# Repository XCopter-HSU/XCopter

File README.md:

# XCopter
This is the (main) repository for the XCopter Project from HSU

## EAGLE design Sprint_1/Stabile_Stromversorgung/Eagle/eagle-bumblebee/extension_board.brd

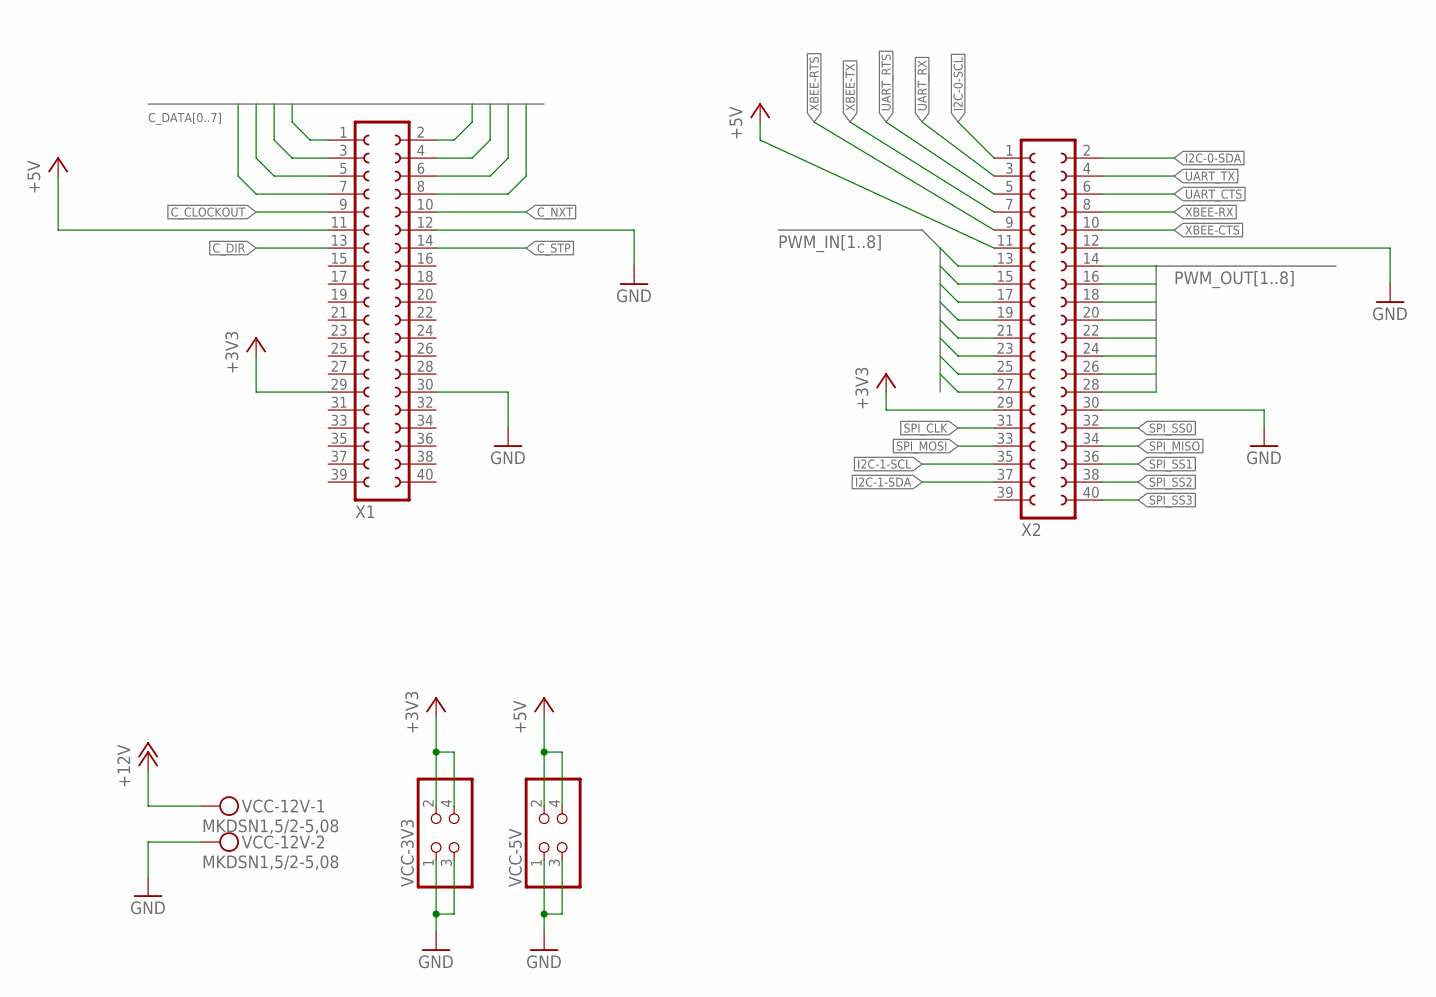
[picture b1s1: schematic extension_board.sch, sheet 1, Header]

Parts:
VCC-3V3, VCC-5V: PINHD-2X2; 2X02
VCC-12V: MKDSN1,5/2-5,08
X1, X2: FE20-2

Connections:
+3V3: VCC-3V3.2, VCC-3V3.4, X1.29, X2.29; also elsewhere on the board
+5V: VCC-5V.2, VCC-5V.4, X1.11, X2.11; also elsewhere on the board
+12V: VCC-12V.1; also elsewhere on the board
C_CLOCKOUT: X1.9; also elsewhere on the board
C_DATA0: X1.1; also elsewhere on the board
C_DATA1: X1.3; also elsewhere on the board
C_DATA2: X1.5; also elsewhere on the board
C_DATA3: X1.7; also elsewhere on the board
C_DATA4: X1.2; also elsewhere on the board
C_DATA5: X1.4; also elsewhere on the board
C_DATA6: X1.6; also elsewhere on the board
C_DATA7: X1.8; also elsewhere on the board
C_DIR: X1.13; also elsewhere on the board
C_NXT: X1.10; also elsewhere on the board
C_STP: X1.14; also elsewhere on the board
GND: VCC-3V3.1, VCC-3V3.3, VCC-5V.1, VCC-5V.3, VCC-12V.2, X1.12, X1.30, X2.12, X2.30; also elsewhere on the board
I2C-0-SCL: X2.1; also elsewhere on the board
I2C-0-SDA: X2.2; also elsewhere on the board
I2C-1-SCL: X2.35; also elsewhere on the board
I2C-1-SDA: X2.37; also elsewhere on the board
PWM_INPUT1: X2.13; also elsewhere on the board
PWM_INPUT2: X2.15; also elsewhere on the board
PWM_INPUT3: X2.17; also elsewhere on the board
PWM_INPUT4: X2.19; also elsewhere on the board
PWM_INPUT5: X2.21; also elsewhere on the board
PWM_INPUT6: X2.23; also elsewhere on the board
PWM_INPUT7: X2.25; also elsewhere on the board
PWM_INPUT8: X2.27; also elsewhere on the board
PWM_OUTPUT1: X2.28; also elsewhere on the board
PWM_OUTPUT2: X2.26; also elsewhere on the board
PWM_OUTPUT3: X2.24; also elsewhere on the board
PWM_OUTPUT4: X2.22; also elsewhere on the board
PWM_OUTPUT5: X2.20; also elsewhere on the board
PWM_OUTPUT6: X2.18; also elsewhere on the board
PWM_OUTPUT7: X2.16; also elsewhere on the board
PWM_OUTPUT8: X2.14; also elsewhere on the board
SPI_CLK: X2.31; also elsewhere on the board
SPI_MISO: X2.34; also elsewhere on the board
SPI_MOSI: X2.33; also elsewhere on the board
SPI_SS0: X2.32; also elsewhere on the board
SPI_SS1: X2.36; also elsewhere on the board
SPI_SS2: X2.38; also elsewhere on the board
SPI_SS3: X2.40; also elsewhere on the board
UART_CTS: X2.6; also elsewhere on the board
UART_RTS: X2.5; also elsewhere on the board
UART_RX: X2.3; also elsewhere on the board
UART_TX: X2.4; also elsewhere on the board
XBEE-CTS: X2.10; also elsewhere on the board
XBEE-RTS: X2.9; also elsewhere on the board
XBEE-RX: X2.8; also elsewhere on the board
XBEE-TX: X2.7; also elsewhere on the board

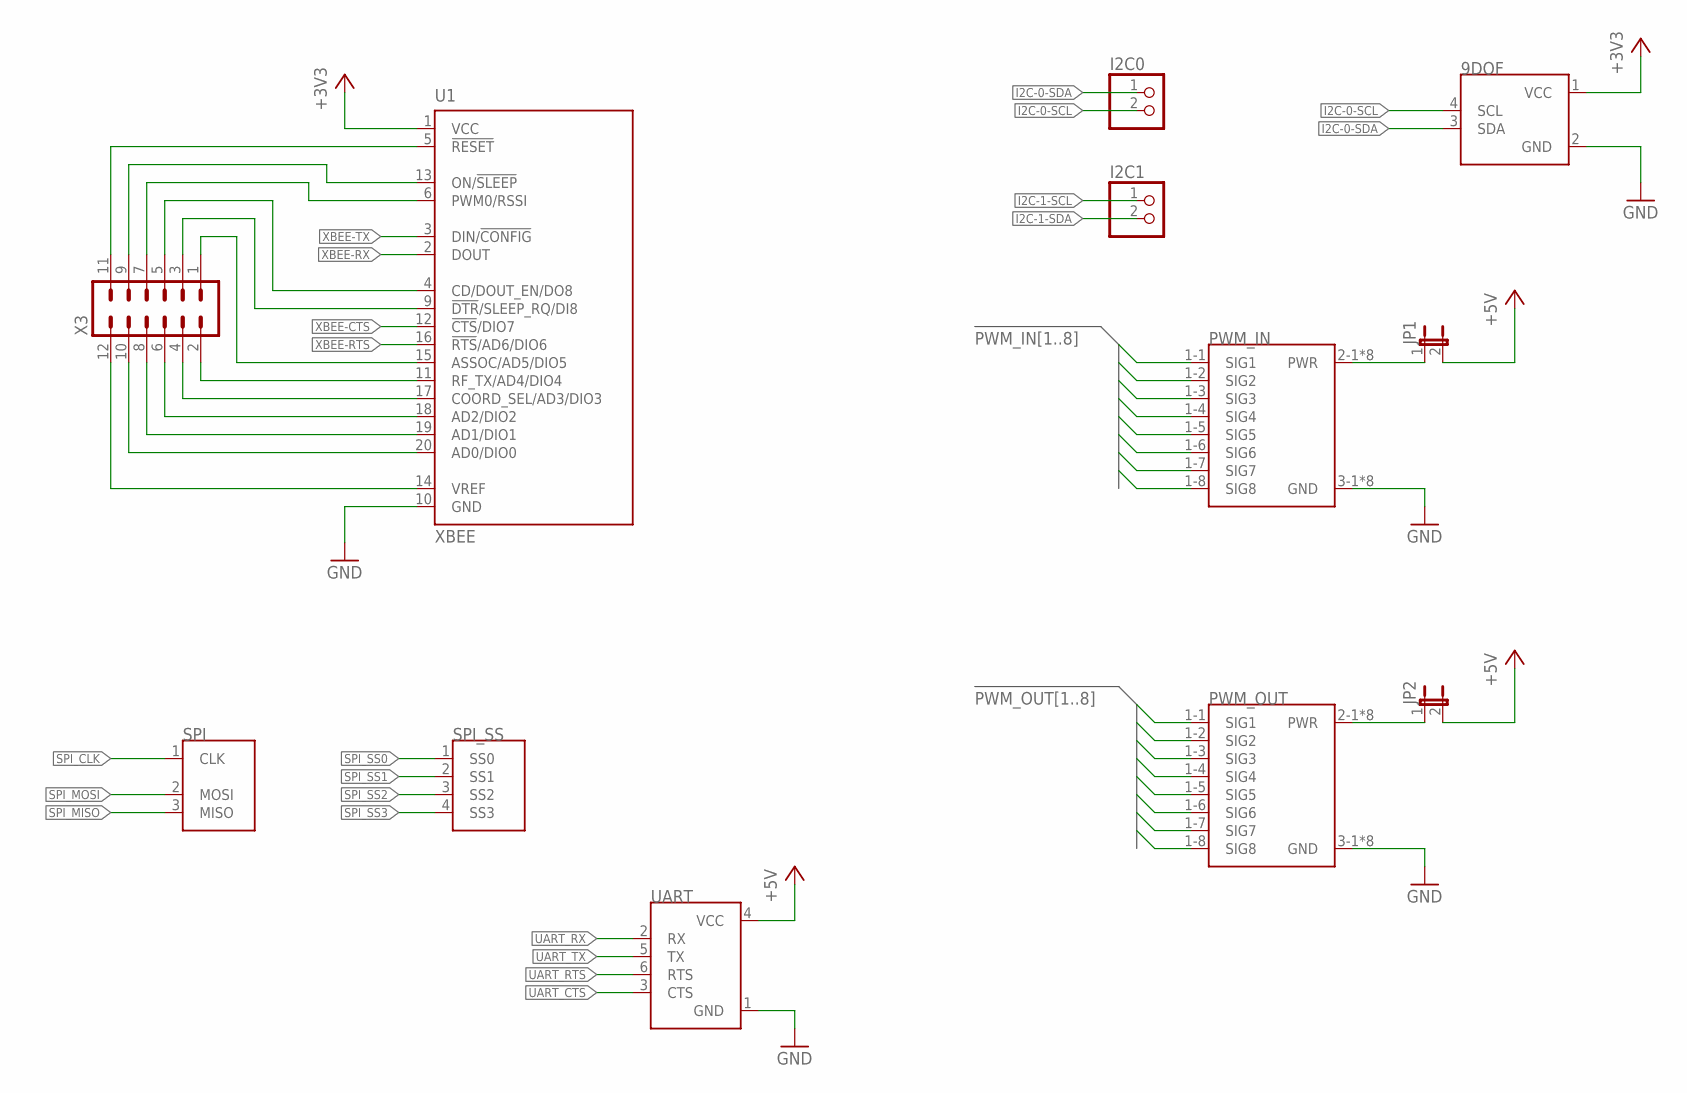
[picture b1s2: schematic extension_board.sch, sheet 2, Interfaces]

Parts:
9DOF: I2C; MA04-1
I2C0, I2C1: PINHD-1X2; 1X02
JP1, JP2: JP1E; JP1
PWM_IN: 8RX; MA08-3
PWM_OUT: 8RX; MA08-3
SPI: SPI_MAIN; MA03-1
SPI_SS: SPI_SS; MA04-1
U1: XBEE
UART: UART; MA03-2
X3: MA06-2

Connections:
+3V3: 9DOF.1 (VCC), U1.1 (VCC); also elsewhere on the board
+5V: JP1.2, JP2.2, UART.4 (VCC); also elsewhere on the board
GND: 9DOF.2 (GND), PWM_IN.3-1 (GND), PWM_IN.3-2 (GND), PWM_IN.3-3 (GND), PWM_IN.3-4 (GND), PWM_IN.3-5 (GND), PWM_IN.3-6 (GND), PWM_IN.3-7 (GND), PWM_IN.3-8 (GND), PWM_OUT.3-1 (GND), PWM_OUT.3-2 (GND), PWM_OUT.3-3 (GND), PWM_OUT.3-4 (GND), PWM_OUT.3-5 (GND), PWM_OUT.3-6 (GND), PWM_OUT.3-7 (GND), PWM_OUT.3-8 (GND), U1.10 (GND), UART.1 (GND); also elsewhere on the board
I2C-0-SCL: 9DOF.4 (SCL), I2C0.2; also elsewhere on the board
I2C-0-SDA: 9DOF.3 (SDA), I2C0.1; also elsewhere on the board
I2C-1-SCL: I2C1.1; also elsewhere on the board
I2C-1-SDA: I2C1.2; also elsewhere on the board
unnamed: JP1.1, PWM_IN.2-1 (PWR), PWM_IN.2-2 (PWR), PWM_IN.2-3 (PWR), PWM_IN.2-4 (PWR), PWM_IN.2-5 (PWR), PWM_IN.2-6 (PWR), PWM_IN.2-7 (PWR), PWM_IN.2-8 (PWR)
unnamed: JP2.1, PWM_OUT.2-1 (PWR), PWM_OUT.2-2 (PWR), PWM_OUT.2-3 (PWR), PWM_OUT.2-4 (PWR), PWM_OUT.2-5 (PWR), PWM_OUT.2-6 (PWR), PWM_OUT.2-7 (PWR), PWM_OUT.2-8 (PWR)
unnamed: U1.5 (!RESET), X3.11
unnamed: U1.14 (VREF), X3.12
unnamed: U1.20 (AD0/DIO0), X3.10
unnamed: U1.19 (AD1/DIO1), X3.8
unnamed: U1.18 (AD2/DIO2), X3.6
unnamed: U1.17 (COORD_SEL/AD3/DIO3), X3.4
unnamed: U1.11 (RF_TX/AD4/DIO4), X3.2
unnamed: U1.15 (ASSOC/AD5/DIO5), X3.1
unnamed: U1.9 (!DTR!/SLEEP_RQ/DI8), X3.3
unnamed: U1.4 (CD/DOUT_EN/DO8), X3.5
unnamed: U1.6 (PWM0/RSSI), X3.7
unnamed: U1.13 (ON/!SLEEP), X3.9
PWM_INPUT1: PWM_IN.1-1 (SIG1); also elsewhere on the board
PWM_INPUT2: PWM_IN.1-2 (SIG2); also elsewhere on the board
PWM_INPUT3: PWM_IN.1-3 (SIG3); also elsewhere on the board
PWM_INPUT4: PWM_IN.1-4 (SIG4); also elsewhere on the board
PWM_INPUT5: PWM_IN.1-5 (SIG5); also elsewhere on the board
PWM_INPUT6: PWM_IN.1-6 (SIG6); also elsewhere on the board
PWM_INPUT7: PWM_IN.1-7 (SIG7); also elsewhere on the board
PWM_INPUT8: PWM_IN.1-8 (SIG8); also elsewhere on the board
PWM_OUTPUT1: PWM_OUT.1-1 (SIG1); also elsewhere on the board
PWM_OUTPUT2: PWM_OUT.1-2 (SIG2); also elsewhere on the board
PWM_OUTPUT3: PWM_OUT.1-3 (SIG3); also elsewhere on the board
PWM_OUTPUT4: PWM_OUT.1-4 (SIG4); also elsewhere on the board
PWM_OUTPUT5: PWM_OUT.1-5 (SIG5); also elsewhere on the board
PWM_OUTPUT6: PWM_OUT.1-6 (SIG6); also elsewhere on the board
PWM_OUTPUT7: PWM_OUT.1-7 (SIG7); also elsewhere on the board
PWM_OUTPUT8: PWM_OUT.1-8 (SIG8); also elsewhere on the board
SPI_CLK: SPI.1 (CLK); also elsewhere on the board
SPI_MISO: SPI.3 (MISO); also elsewhere on the board
SPI_MOSI: SPI.2 (MOSI); also elsewhere on the board
SPI_SS0: SPI_SS.1 (SS0); also elsewhere on the board
SPI_SS1: SPI_SS.2 (SS1); also elsewhere on the board
SPI_SS2: SPI_SS.3 (SS2); also elsewhere on the board
SPI_SS3: SPI_SS.4 (SS3); also elsewhere on the board
UART_CTS: UART.3 (CTS); also elsewhere on the board
UART_RTS: UART.6 (RTS); also elsewhere on the board
UART_RX: UART.2 (RX); also elsewhere on the board
UART_TX: UART.5 (TX); also elsewhere on the board
XBEE-CTS: U1.12 (!CTS!/DIO7); also elsewhere on the board
XBEE-RTS: U1.16 (!RTS!/AD6/DIO6); also elsewhere on the board
XBEE-RX: U1.2 (DOUT); also elsewhere on the board
XBEE-TX: U1.3 (DIN/!CONFIG); also elsewhere on the board

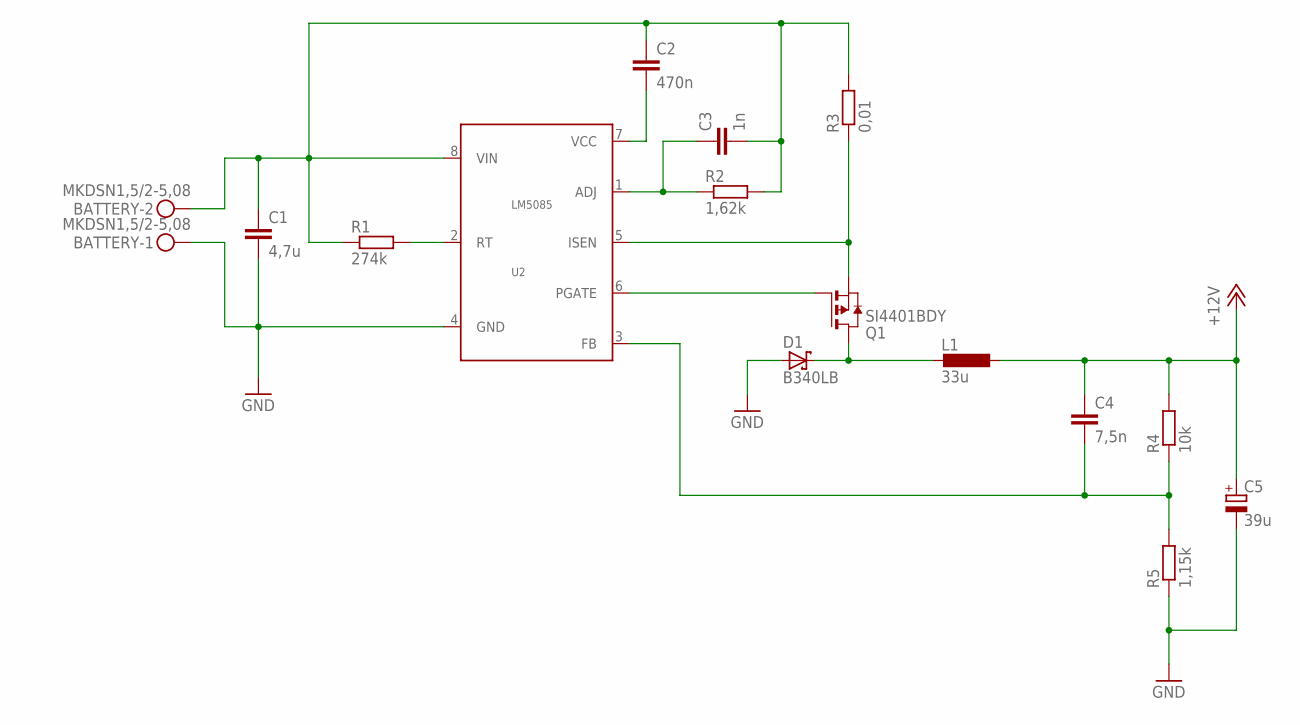
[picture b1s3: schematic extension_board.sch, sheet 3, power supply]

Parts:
BATTERY: MKDSN1,5/2-5,08
C1: 4,7u; C1206
C2: 470n; C1206
C3: 1n; C1206
C4: 7,5n; C1206
C5: 39u; SMC_B
D1: B340LB; SMB
L1: 33u; INDUKTOR
Q1: SI4401BDY; SO8-FET
R1: 274k; R1206
R2: 1,62k; R1206
R3: 0,01; R1206
R4: 10k; R1206
R5: 1,15k; R1206
U2: LM5085; S-PDSO-G08

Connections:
+12V: C4.1, C5.+, L1.P$2 (2), R4.2; also elsewhere on the board
GND: BATTERY.1, C1.2, C5.-, D1.A, R5.1, U2.4 (GND); also elsewhere on the board
unnamed: R1.2, U2.2 (RT)
unnamed: C2.2, U2.7 (VCC)
unnamed: C3.1, R2.1, U2.1 (ADJ)
unnamed: BATTERY.2, C1.1, C2.1, C3.2, R1.1, R2.2, R3.2, U2.8 (VIN)
unnamed: Q1.1 (S), Q1.2 (S), Q1.3 (S), R3.1, U2.5 (ISEN)
unnamed: C4.2, R4.1, R5.2, U2.3 (FB)
unnamed: Q1.4 (G), U2.6 (PGATE)
unnamed: D1.C, L1.P$1 (1), Q1.5 (D), Q1.6 (D), Q1.7 (D), Q1.8 (D), Q1.D1 (D), Q1.D2 (D), Q1.D3 (D)

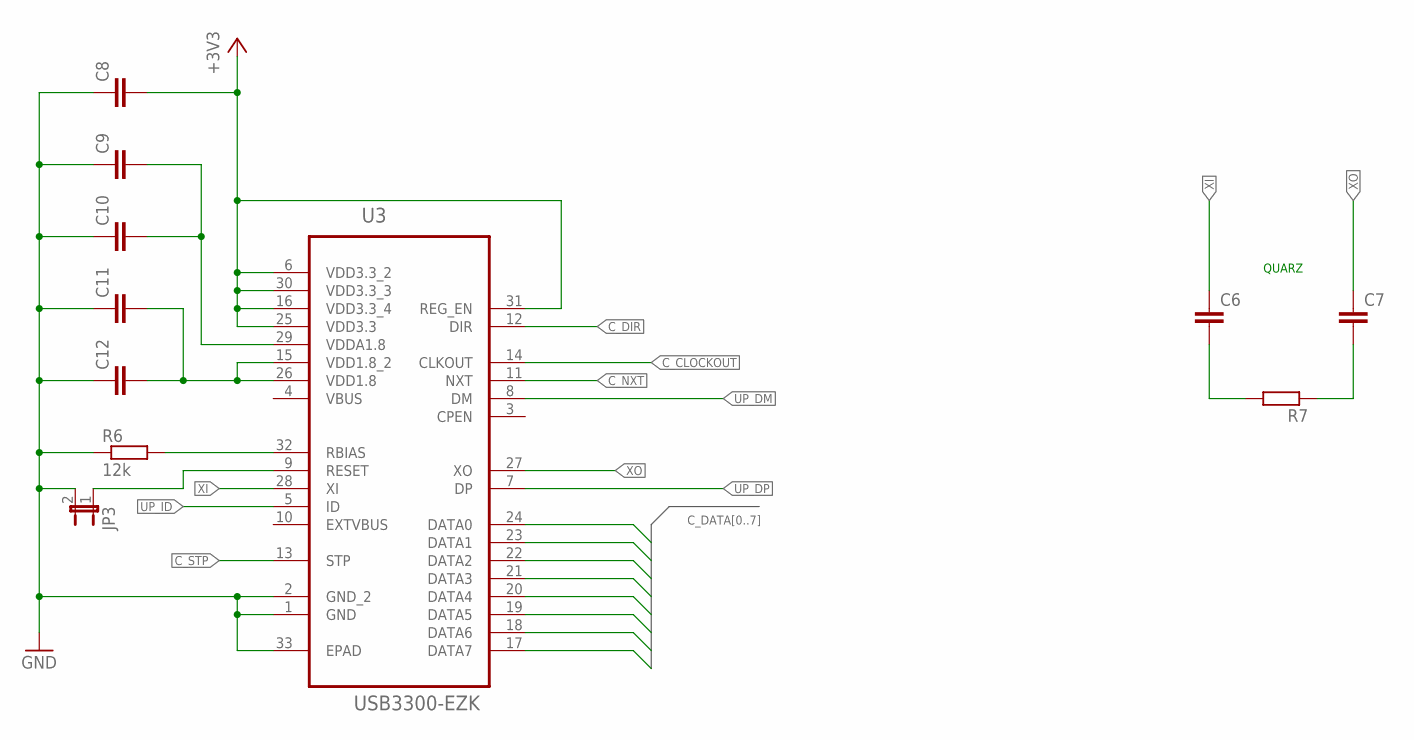
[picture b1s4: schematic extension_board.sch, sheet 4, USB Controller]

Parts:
C6, C7, C8, C9, C10, C11, C12: CC1206; C1206
JP3: JP1E; JP1
R6: 12k; R1206
R7: RR1206; R1206
U3: USB3300-EZK; QFN50P500X500X100-33N

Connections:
+3V3: C8.2, U3.6 (VDD3.3_2), U3.16 (VDD3.3_4), U3.25 (VDD3.3), U3.30 (VDD3.3_3), U3.31 (REG_EN); also elsewhere on the board
C_CLOCKOUT: U3.14 (CLKOUT); also elsewhere on the board
C_DATA0: U3.24 (DATA0); also elsewhere on the board
C_DATA1: U3.23 (DATA1); also elsewhere on the board
C_DATA2: U3.22 (DATA2); also elsewhere on the board
C_DATA3: U3.21 (DATA3); also elsewhere on the board
C_DATA4: U3.20 (DATA4); also elsewhere on the board
C_DATA5: U3.19 (DATA5); also elsewhere on the board
C_DATA6: U3.18 (DATA6); also elsewhere on the board
C_DATA7: U3.17 (DATA7); also elsewhere on the board
C_DIR: U3.12 (DIR); also elsewhere on the board
C_NXT: U3.11 (NXT); also elsewhere on the board
C_STP: U3.13 (STP); also elsewhere on the board
GND: C8.1, C9.1, C10.1, C11.1, C12.1, JP3.2, R6.1, U3.1 (GND), U3.2 (GND_2), U3.33 (EPAD); also elsewhere on the board
unnamed: C9.2, C10.2, U3.29 (VDDA1.8)
unnamed: R6.2, U3.32 (RBIAS)
unnamed: C6.2, R7.2
unnamed: C7.2, R7.1
unnamed: C11.2, C12.2, U3.15 (VDD1.8_2), U3.26 (VDD1.8)
unnamed: JP3.1, U3.9 (RESET)
UP_DM: U3.8 (DM)
UP_DP: U3.7 (DP)
UP_ID: U3.5 (ID)
VBUS: U3.4 (VBUS)
XI: C6.1, U3.28 (XI)
XO: C7.1, U3.27 (XO)

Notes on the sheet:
QUARZ

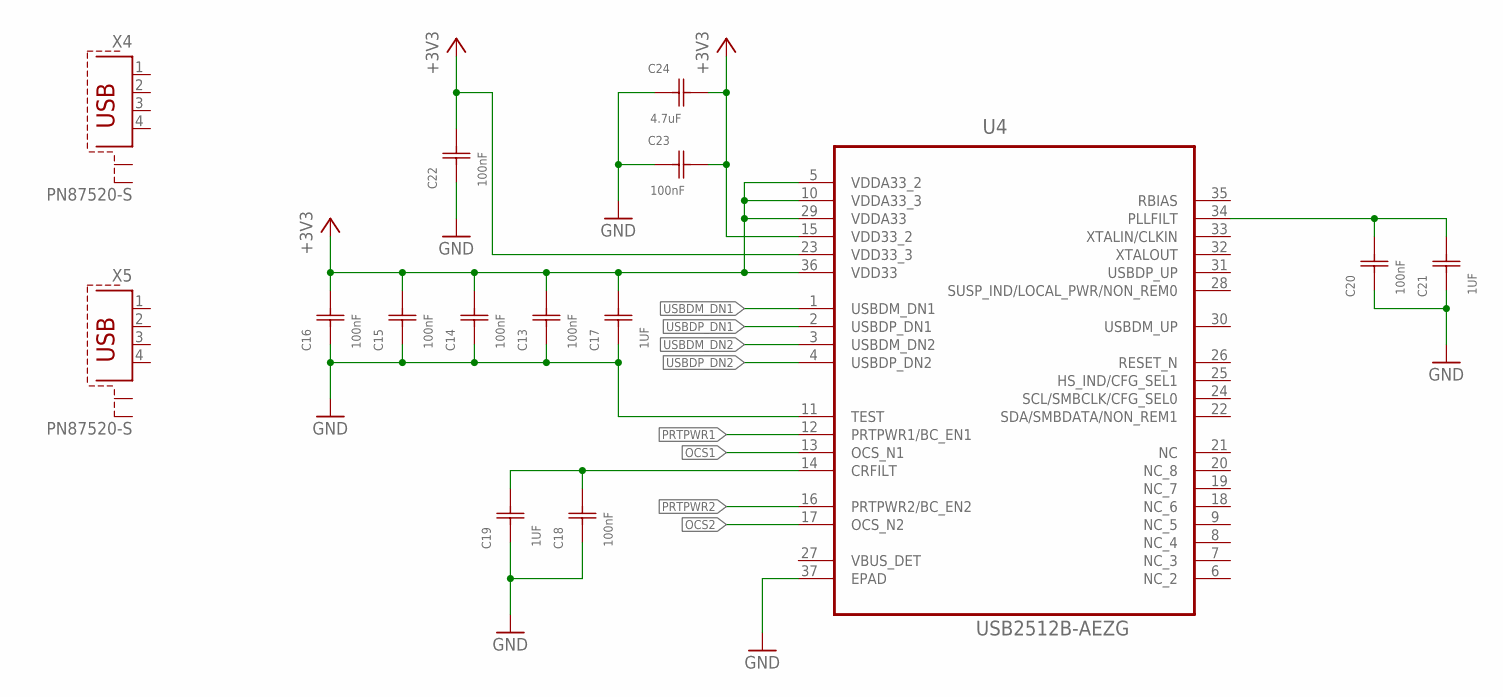
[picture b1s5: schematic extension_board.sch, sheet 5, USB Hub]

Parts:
C13, C14, C15, C16, C18, C20, C22, C23: 100nF; CAPC1608X90N
C17, C19, C21: 1UF; CAPC3216X127N
C24: 4.7uF; CAPC2013X140N
U4: USB2512B-AEZG; QFN50P600X600X100-37N
X4, X5: PN87520-S

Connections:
+3V3: C13.2 (C2), C14.2 (C2), C15.2 (C2), C16.2 (C2), C17.2 (C2), C22.2 (C2), C23.2 (C2), C24.2 (C2), U4.5 (VDDA33_2), U4.10 (VDDA33_3), U4.15 (VDD33_2), U4.23 (VDD33_3), U4.29 (VDDA33), U4.36 (VDD33); also elsewhere on the board
GND: C13.1 (C1), C14.1 (C1), C15.1 (C1), C16.1 (C1), C17.1 (C1), C18.1 (C1), C19.1 (C1), C20.1 (C1), C21.1 (C1), C22.1 (C1), C23.1 (C1), C24.1 (C1), U4.11 (TEST), U4.37 (EPAD); also elsewhere on the board
unnamed: C18.2 (C2), C19.2 (C2), U4.14 (CRFILT)
unnamed: C20.2 (C2), C21.2 (C2), U4.34 (PLLFILT)
OCS1: U4.13 (OCS_N1)
OCS2: U4.17 (OCS_N2)
PRTPWR1: U4.12 (PRTPWR1/BC_EN1)
PRTPWR2: U4.16 (PRTPWR2/BC_EN2)
USBDM_DN1: U4.1 (USBDM_DN1)
USBDM_DN2: U4.3 (USBDM_DN2)
USBDP_DN1: U4.2 (USBDP_DN1)
USBDP_DN2: U4.4 (USBDP_DN2)
VBUS_DET: U4.27 (VBUS_DET)

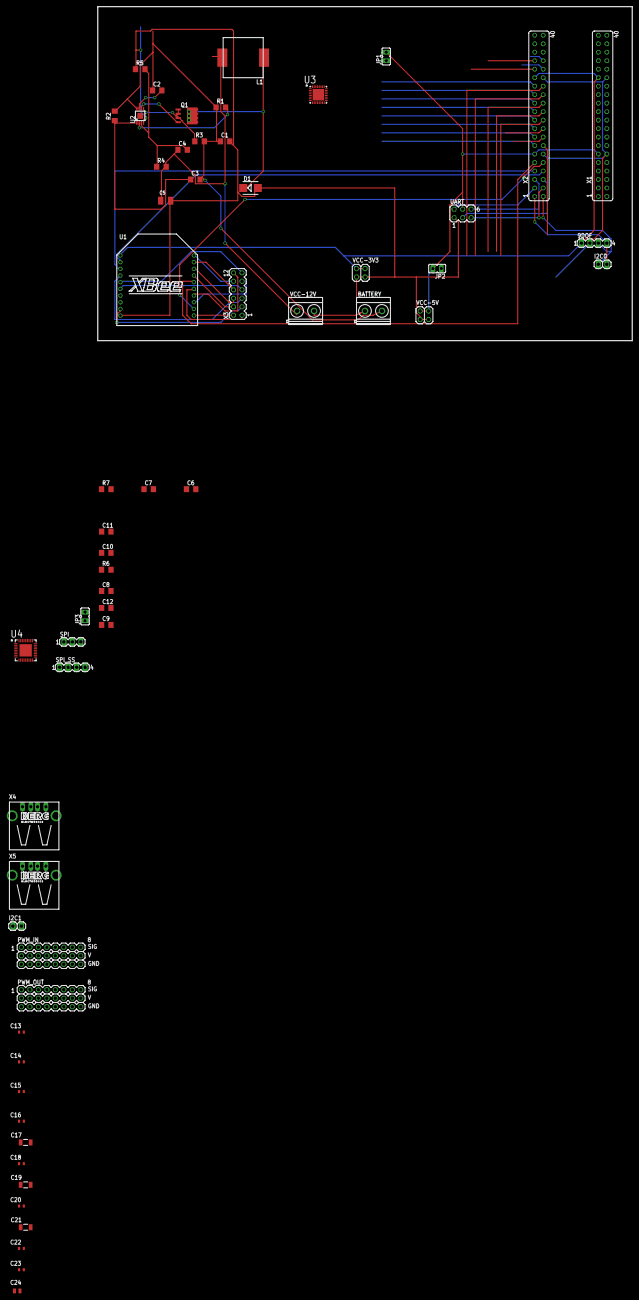
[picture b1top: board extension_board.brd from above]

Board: 2 copper layers, 160.0 x 100.0 mm, 58 parts (0 on the bottom side), 83 nets.

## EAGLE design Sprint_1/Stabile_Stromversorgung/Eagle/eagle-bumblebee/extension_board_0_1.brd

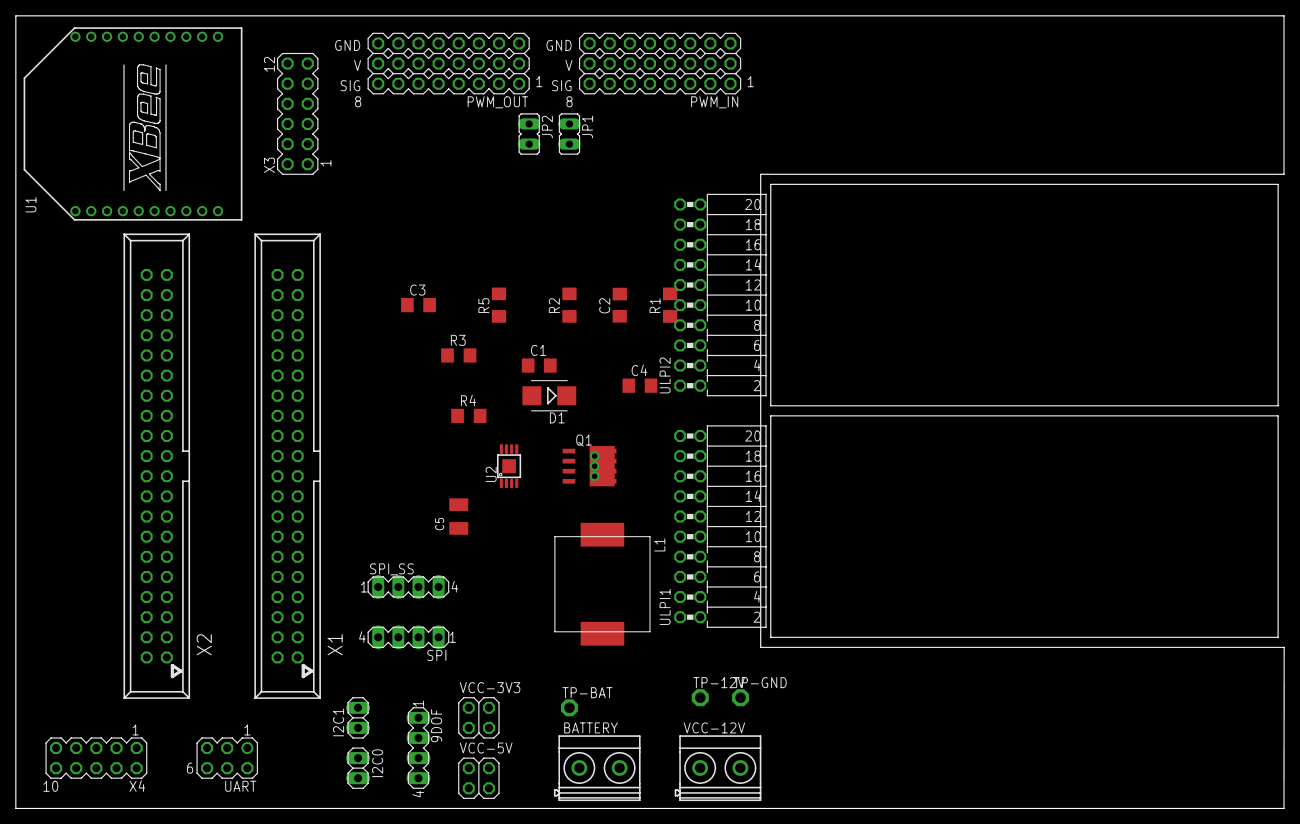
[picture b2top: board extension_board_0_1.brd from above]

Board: 2 copper layers, 160.0 x 100.0 mm, 38 parts (0 on the bottom side), 98 nets, no tracks yet.

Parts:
9DOF: I2C; MA04-1
BATTERY: MKDSN1,5/2-5,08
C1: 4,7u; C1206
C2: 470n; C1206
C3: 1n; C1206
C4: 7,5n; C1206
C5: 39u; SMC_B
D1: B340LB; SMB
I2C0, I2C1: 1X02
JP1, JP2: JP1
L1: 33u; INDUKTOR
PWM_IN: 8RX; MA08-3
PWM_OUT: 8RX; MA08-3
Q1: SI4401BDY; SO8-FET
R1: 274k; R1206
R2: 1,62k; R1206
R3: 0,01; R1206
R4: 10k; R1206
R5: 1,15k; R1206
SPI: SPI_MAIN; MA04-1
SPI_SS: SPI_SS; MA04-1
TP-12V: TPPAD1-13; P1-13
TP-BAT: TPPAD1-13; P1-13
TP-GND: TPPAD1-13; P1-13
U1: XBEE
U2: LM5085; S-PDSO-G08
UART: UART; MA03-2
ULPI1, ULPI2: FE10-2W
VCC-3V3, VCC-5V: 2X02
VCC-12V: MKDSN1,5/2-5,08
X1, X2: 057-040-1
X3: MA06-2
X4: MA05-2

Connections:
+3V3: 9DOF.1, U1.1, ULPI1.19, ULPI1.20, ULPI2.19, ULPI2.20, VCC-3V3.2, VCC-3V3.4, X1.29, X2.29
+5V: JP1.2, JP2.2, UART.4, ULPI1.2, ULPI1.4, ULPI2.2, ULPI2.4, VCC-5V.2, VCC-5V.4, X1.11, X2.11
+12V: C4.1, C5.+, L1.P$2, R4.2, TP-12V.TP, VCC-12V.1
GND: 9DOF.2, BATTERY.1, C1.2, C5.-, D1.A, PWM_IN.3-1, PWM_IN.3-2, PWM_IN.3-3, PWM_IN.3-4, PWM_IN.3-5, PWM_IN.3-6, PWM_IN.3-7, PWM_IN.3-8, PWM_OUT.3-1, PWM_OUT.3-2, PWM_OUT.3-3, PWM_OUT.3-4, PWM_OUT.3-5, PWM_OUT.3-6, PWM_OUT.3-7, PWM_OUT.3-8, R5.1, TP-GND.TP, U1.10, U2.4, UART.1, ULPI1.17, ULPI1.18, ULPI2.17, ULPI2.18, VCC-3V3.1, VCC-3V3.3, VCC-5V.1, VCC-5V.3, VCC-12V.2, X1.12, X1.30, X2.12, X2.30
GPIO0: X2.31, X4.1
GPIO1: X2.32, X4.2
GPIO2: X2.33, X4.3
GPIO3: X2.34, X4.4
GPIO4: X2.35, X4.5
GPIO5: X2.36, X4.6
GPIO6: X2.37, X4.7
GPIO7: X2.38, X4.8
GPIO8: X2.39, X4.9
GPIO9: X2.40, X4.10
I2C-0-SCL: 9DOF.4, I2C0.2, X2.2
I2C-0-SDA: 9DOF.3, I2C0.1, X2.1
I2C-1-SCL: I2C1.1, X1.2
I2C-1-SDA: I2C1.2, X1.1
unnamed: R1.2, U2.2
unnamed: C2.2, U2.7
unnamed: C3.1, R2.1, U2.1
unnamed: BATTERY.2, C1.1, C2.1, C3.2, R1.1, R2.2, R3.2, TP-BAT.TP, U2.8
unnamed: Q1.1, Q1.2, Q1.3, R3.1, U2.5
unnamed: C4.2, R4.1, R5.2, U2.3
unnamed: Q1.4, U2.6
unnamed: D1.C, L1.P$1, Q1.5, Q1.6, Q1.7, Q1.8, Q1.D1, Q1.D2, Q1.D3
unnamed: JP1.1, PWM_IN.2-1, PWM_IN.2-2, PWM_IN.2-3, PWM_IN.2-4, PWM_IN.2-5, PWM_IN.2-6, PWM_IN.2-7, PWM_IN.2-8
unnamed: JP2.1, PWM_OUT.2-1, PWM_OUT.2-2, PWM_OUT.2-3, PWM_OUT.2-4, PWM_OUT.2-5, PWM_OUT.2-6, PWM_OUT.2-7, PWM_OUT.2-8
unnamed: U1.5, X3.11
unnamed: U1.14, X3.12
unnamed: U1.20, X3.10
unnamed: U1.19, X3.8
unnamed: U1.18, X3.6
unnamed: U1.17, X3.4
unnamed: U1.11, X3.2
unnamed: U1.15, X3.1
unnamed: U1.9, X3.3
unnamed: U1.4, X3.5
unnamed: U1.6, X3.7
unnamed: U1.13, X3.9
PWM_IN1: PWM_IN.1-1, X2.13
PWM_IN2: PWM_IN.1-2, X2.14
PWM_IN3: PWM_IN.1-3, X2.15
PWM_IN4: PWM_IN.1-4, X2.16
PWM_IN5: PWM_IN.1-5, X2.17
PWM_IN6: PWM_IN.1-6, X2.18
PWM_IN7: PWM_IN.1-7, X2.19
PWM_IN8: PWM_IN.1-8, X2.20
PWM_OUT1: PWM_OUT.1-1, X2.21
PWM_OUT2: PWM_OUT.1-2, X2.22
PWM_OUT3: PWM_OUT.1-3, X2.23
PWM_OUT4: PWM_OUT.1-4, X2.24
PWM_OUT5: PWM_OUT.1-5, X2.25
PWM_OUT6: PWM_OUT.1-6, X2.26
PWM_OUT7: PWM_OUT.1-7, X2.27
PWM_OUT8: PWM_OUT.1-8, X2.28
SPI_CLK: SPI.1, X1.3
SPI_MISO: SPI.4, X1.5
SPI_MOSI: SPI.3, X1.4
SPI_SS: SPI.2, X1.6
SPI_SS0: SPI_SS.1, X1.7
SPI_SS1: SPI_SS.2, X1.8
SPI_SS2: SPI_SS.3, X1.9
SPI_SS3: SPI_SS.4, X1.10
UART_CTS: UART.3, X2.10
UART_RTS: UART.6, X2.9
UART_RX: UART.2, X2.7
UART_TX: UART.5, X2.8
ULPI1_CLK: ULPI1.10, X1.14
ULPI1_D0: ULPI1.1, X1.25
ULPI1_D1: ULPI1.3, X1.24
ULPI1_D2: ULPI1.5, X1.23
ULPI1_D3: ULPI1.7, X1.22
ULPI1_D4: ULPI1.9, X1.21
ULPI1_D5: ULPI1.11, X1.20
ULPI1_D6: ULPI1.13, X1.19
ULPI1_D7: ULPI1.15, X1.18
ULPI1_DIR: ULPI1.12, X1.15
ULPI1_NXT: ULPI1.14, X1.16
ULPI1_RST: ULPI1.8, X1.13
ULPI1_STP: ULPI1.16, X1.17
ULPI2_CLK: ULPI2.10, X1.27
ULPI2_D0: ULPI2.1, X1.40
ULPI2_D1: ULPI2.3, X1.39
ULPI2_D2: ULPI2.5, X1.38
ULPI2_D3: ULPI2.7, X1.37
ULPI2_D4: ULPI2.9, X1.36
ULPI2_D5: ULPI2.11, X1.35
ULPI2_D6: ULPI2.13, X1.34
ULPI2_D7: ULPI2.15, X1.33
ULPI2_DIR: ULPI2.12, X1.28
ULPI2_NXT: ULPI2.14, X1.31
ULPI2_RST: ULPI2.8, X1.26
ULPI2_STP: ULPI2.16, X1.32
XBEE-CTS: U1.12, X2.5
XBEE-RTS: U1.16, X2.6
XBEE-RX: U1.2, X2.4
XBEE-TX: U1.3, X2.3

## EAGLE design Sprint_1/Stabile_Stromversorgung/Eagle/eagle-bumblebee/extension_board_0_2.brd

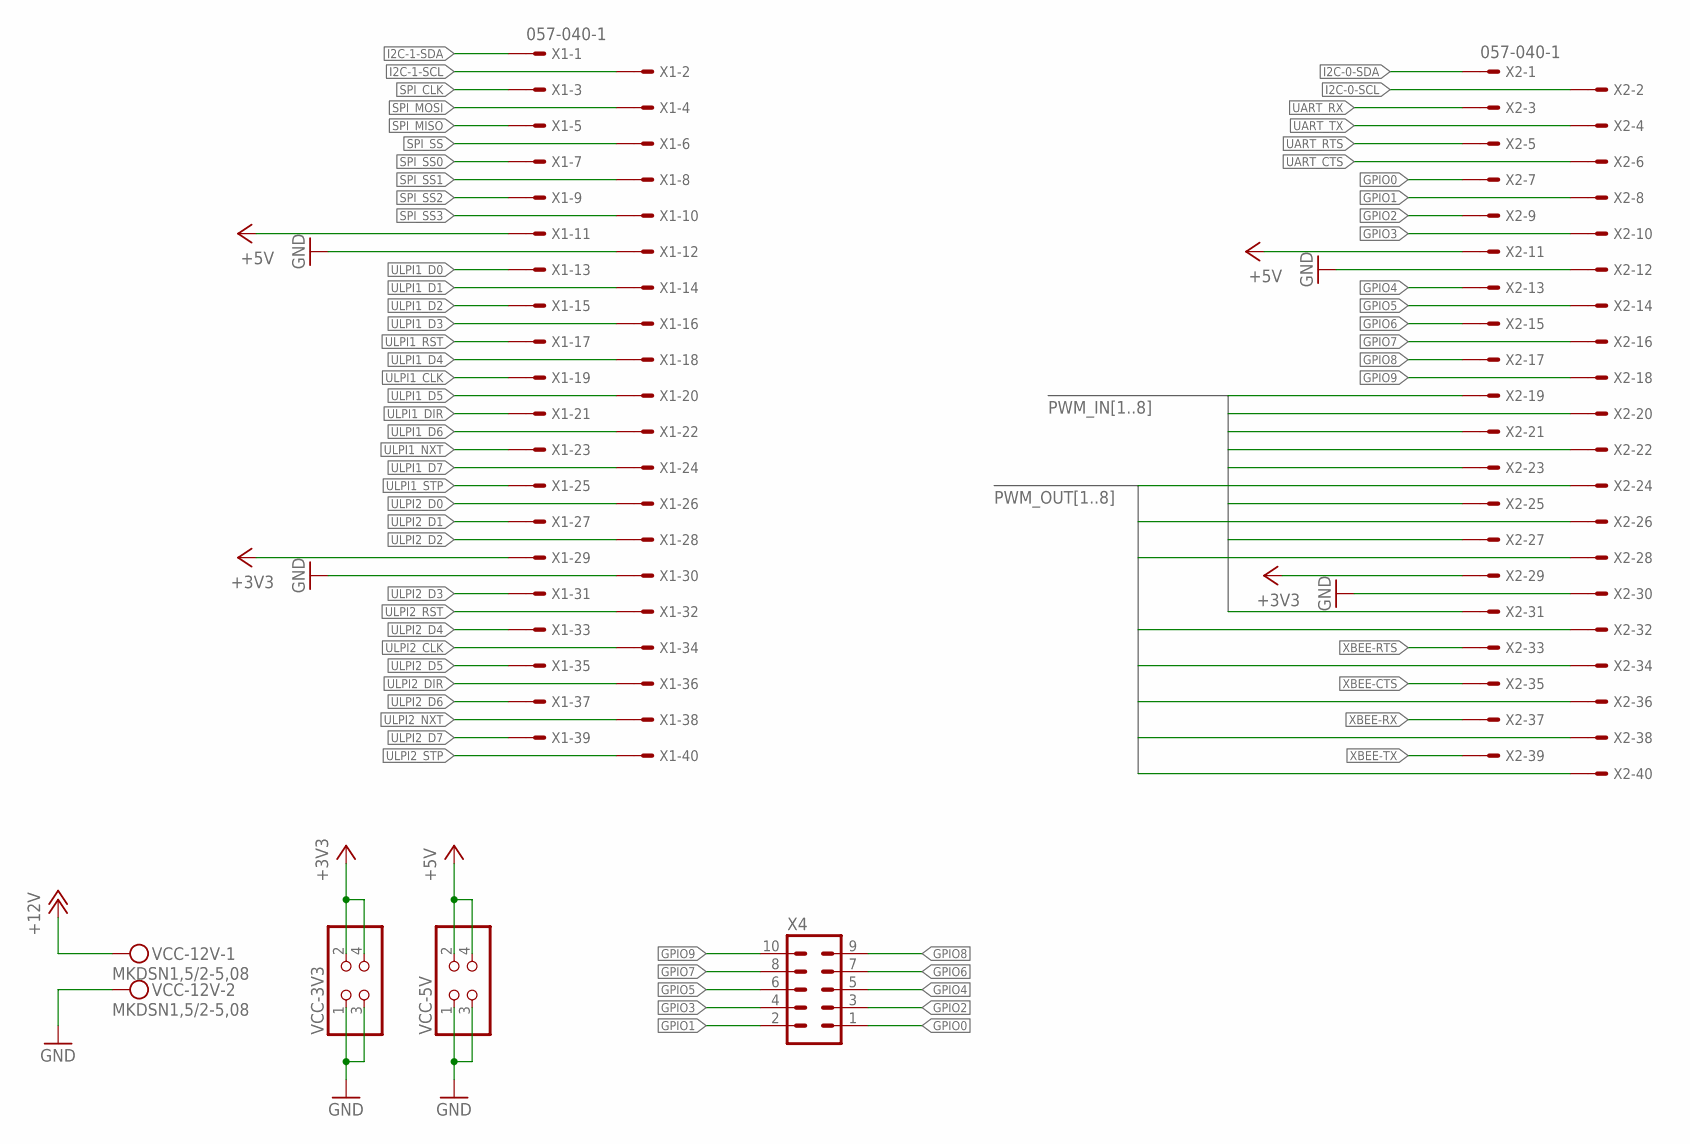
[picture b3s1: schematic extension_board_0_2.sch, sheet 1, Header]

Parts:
VCC-3V3, VCC-5V: PINHD-2X2; 2X02
VCC-12V: MKDSN1,5/2-5,08
X1, X2: 057-040-1
X4: MA05-2

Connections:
+3V3: VCC-3V3.2, VCC-3V3.4, X1.29, X2.29; also elsewhere on the board
+5V: VCC-5V.2, VCC-5V.4, X1.11, X2.11; also elsewhere on the board
+12V: VCC-12V.1; also elsewhere on the board
GND: VCC-3V3.1, VCC-3V3.3, VCC-5V.1, VCC-5V.3, VCC-12V.2, X1.12, X1.30, X2.12, X2.30; also elsewhere on the board
GPIO0: X2.7, X4.1
GPIO1: X2.8, X4.2
GPIO2: X2.9, X4.3
GPIO3: X2.10, X4.4
GPIO4: X2.13, X4.5
GPIO5: X2.14, X4.6
GPIO6: X2.15, X4.7
GPIO7: X2.16, X4.8
GPIO8: X2.17, X4.9
GPIO9: X2.18, X4.10
I2C-0-SCL: X2.2; also elsewhere on the board
I2C-0-SDA: X2.1; also elsewhere on the board
I2C-1-SCL: X1.2; also elsewhere on the board
I2C-1-SDA: X1.1; also elsewhere on the board
PWM_IN1: X2.19; also elsewhere on the board
PWM_IN2: X2.20; also elsewhere on the board
PWM_IN3: X2.21; also elsewhere on the board
PWM_IN4: X2.22; also elsewhere on the board
PWM_IN5: X2.23; also elsewhere on the board
PWM_IN6: X2.25; also elsewhere on the board
PWM_IN7: X2.27; also elsewhere on the board
PWM_IN8: X2.31; also elsewhere on the board
PWM_OUT1: X2.40; also elsewhere on the board
PWM_OUT2: X2.38; also elsewhere on the board
PWM_OUT3: X2.36; also elsewhere on the board
PWM_OUT4: X2.34; also elsewhere on the board
PWM_OUT5: X2.32; also elsewhere on the board
PWM_OUT6: X2.28; also elsewhere on the board
PWM_OUT7: X2.26; also elsewhere on the board
PWM_OUT8: X2.24; also elsewhere on the board
SPI_CLK: X1.3; also elsewhere on the board
SPI_MISO: X1.5; also elsewhere on the board
SPI_MOSI: X1.4; also elsewhere on the board
SPI_SS: X1.6; also elsewhere on the board
SPI_SS0: X1.7; also elsewhere on the board
SPI_SS1: X1.8; also elsewhere on the board
SPI_SS2: X1.9; also elsewhere on the board
SPI_SS3: X1.10; also elsewhere on the board
UART_CTS: X2.6; also elsewhere on the board
UART_RTS: X2.5; also elsewhere on the board
UART_RX: X2.3; also elsewhere on the board
UART_TX: X2.4; also elsewhere on the board
ULPI1_CLK: X1.19; also elsewhere on the board
ULPI1_D0: X1.13; also elsewhere on the board
ULPI1_D1: X1.14; also elsewhere on the board
ULPI1_D2: X1.15; also elsewhere on the board
ULPI1_D3: X1.16; also elsewhere on the board
ULPI1_D4: X1.18; also elsewhere on the board
ULPI1_D5: X1.20; also elsewhere on the board
ULPI1_D6: X1.22; also elsewhere on the board
ULPI1_D7: X1.24; also elsewhere on the board
ULPI1_DIR: X1.21; also elsewhere on the board
ULPI1_NXT: X1.23; also elsewhere on the board
ULPI1_RST: X1.17; also elsewhere on the board
ULPI1_STP: X1.25; also elsewhere on the board
ULPI2_CLK: X1.34; also elsewhere on the board
ULPI2_D0: X1.26; also elsewhere on the board
ULPI2_D1: X1.27; also elsewhere on the board
ULPI2_D2: X1.28; also elsewhere on the board
ULPI2_D3: X1.31; also elsewhere on the board
ULPI2_D4: X1.33; also elsewhere on the board
ULPI2_D5: X1.35; also elsewhere on the board
ULPI2_D6: X1.37; also elsewhere on the board
ULPI2_D7: X1.39; also elsewhere on the board
ULPI2_DIR: X1.36; also elsewhere on the board
ULPI2_NXT: X1.38; also elsewhere on the board
ULPI2_RST: X1.32; also elsewhere on the board
ULPI2_STP: X1.40; also elsewhere on the board
XBEE-CTS: X2.35; also elsewhere on the board
XBEE-RTS: X2.33; also elsewhere on the board
XBEE-RX: X2.37; also elsewhere on the board
XBEE-TX: X2.39; also elsewhere on the board
